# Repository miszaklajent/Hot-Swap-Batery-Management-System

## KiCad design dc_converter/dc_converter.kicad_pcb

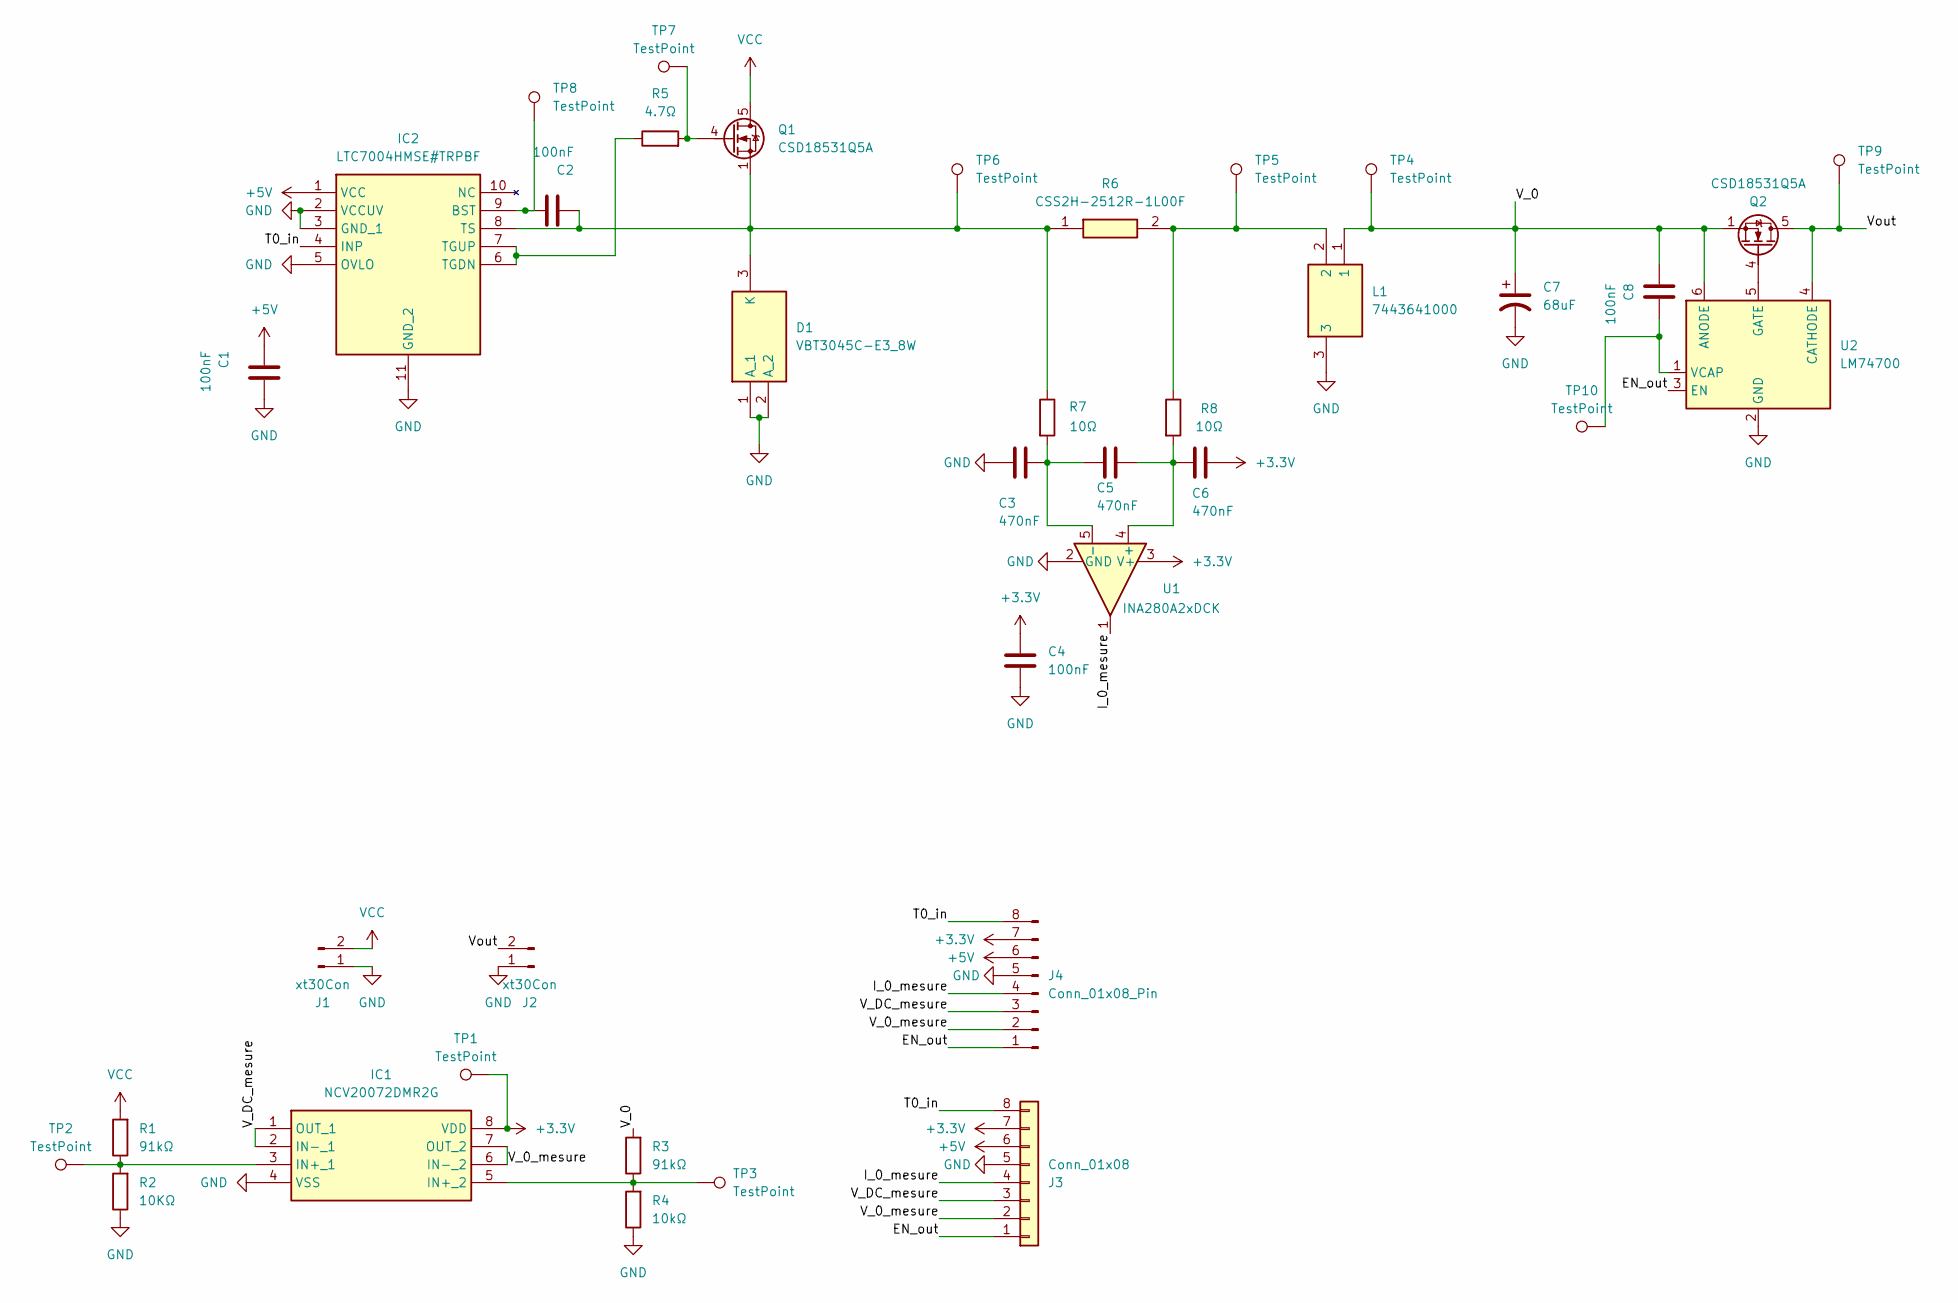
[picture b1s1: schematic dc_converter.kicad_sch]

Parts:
C1, C2, C4, C8: 100nF; C_0402_1005Metric
C3, C5, C6: 470nF; C_0402_1005Metric
C7: 68uF; CAPAE830X1050N
D1: VBT3045C-E3_8W; TO-263AB_1; Mouser Part Number 625-VBT3045C-E3/8W
IC1: NCV20072DMR2G; SOP65P490X110-8N; Mouser Part Number 863-NCV20072DMR2G
IC2: LTC7004HMSE#TRPBF; SOP50P490X110-11N; Mouser Part Number 584-7004HMSETRPBF
J1, J2: xt30Con; AMASS_XT30U-M_1x02_P5.0mm_Vertical
J3: Conn_01x08; JST_GH_SM08B-GHS-TB_1x08-1MP_P1.25mm_Horizontal
J4: Conn_01x08_Pin; PinHeader_1x08_P2.54mm_Vertical
L1: 7443641000; WE-HCF_SMD_HIGH-CURRENT_INDUCTOR; Mouser Part Number 710-7443641000
Q1, Q2: CSD18531Q5A; TDSON-8-1
R1, R3: 91kΩ; R_0402_1005Metric
R2: 10KΩ; R_0402_1005Metric
R4: 10kΩ; R_0402_1005Metric
R5: 4.7Ω; R_1206_3216Metric_Pad1.30x1.75mm_HandSolder
R6: CSS2H-2512R-1L00F; RESC6430X87N; Mouser Part Number 652-CSS2H2512R1L00F
R7, R8: 10Ω; R_0402_1005Metric
TP1, TP2, TP3, TP4, TP5, TP6, TP7, TP8, TP9, TP10: TestPoint; TestPoint_Pad_D1.0mm
U1: INA280A2xDCK; SOT-353_SC-70-5
U2: LM74700; SOT-23-6

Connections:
+3.3V: C4.2, C6.2, IC1.8 (VDD), J3.7, J4.7, TP1.1 (1_1), U1.3 (V+)
+5V: C1.1, IC2.1 (VCC), J3.6, J4.6
/EN_out: J3.1, J4.1, U2.3 (EN)
/I_0_mesure: J3.4, J4.4, U1.1
/T0_in: IC2.4 (INP), J3.8, J4.8
/V_0: C7.1, C8.1, L1.1, Q2.1 (S), Q2.2 (S), Q2.3 (S), R3.2, TP4.1 (1_1), U2.6 (ANODE)
/V_0_mesure: IC1.6 (IN-_2), IC1.7 (OUT_2), J3.2, J4.2
/V_DC_mesure: IC1.1 (OUT_1), IC1.2 (IN-_1), J3.3, J4.3
/Vout: J2.2, Q2.5 (D), TP9.1 (1_1), U2.4 (CATHODE); also elsewhere on the board
GND: C1.2, C3.1, C4.1, C7.2, D1.1 (A_1), D1.2 (A_2), IC1.4 (VSS), IC2.2 (VCCUV), IC2.3 (GND_1), IC2.5 (OVLO), IC2.11 (GND_2), J1.1, J2.1, J3.5, J4.5, L1.3, R2.1, R4.1, U1.2 (GND), U2.2 (GND); also elsewhere on the board
unnamed: C2.1, D1.3 (K), IC2.8 (TS), Q1.1 (S), Q1.2 (S), Q1.3 (S), R6.1, R7.1, TP6.1 (1_1)
unnamed: IC1.3 (IN+_1), R1.1, R2.2, TP2.1 (1_1)
unnamed: IC1.5 (IN+_2), R3.1, R4.2, TP3.1 (1_1)
unnamed: C2.2, IC2.9 (BST), TP8.1 (1_1)
unnamed: IC2.6 (TGDN), IC2.7 (TGUP), R5.1
unnamed: L1.2, R6.2, R8.1, TP5.1 (1_1)
unnamed: Q1.4 (G), R5.2, TP7.1 (1_1)
unnamed: Q2.4 (G), U2.5 (GATE)
unnamed: C5.2, C6.1, R8.2, U1.4 (+)
unnamed: C3.2, C5.1, R7.2, U1.5 (-)
unnamed: C8.2, TP10.1 (1_1), U2.1 (VCAP)
VCC: J1.2, Q1.5 (D), R1.2; also elsewhere on the board

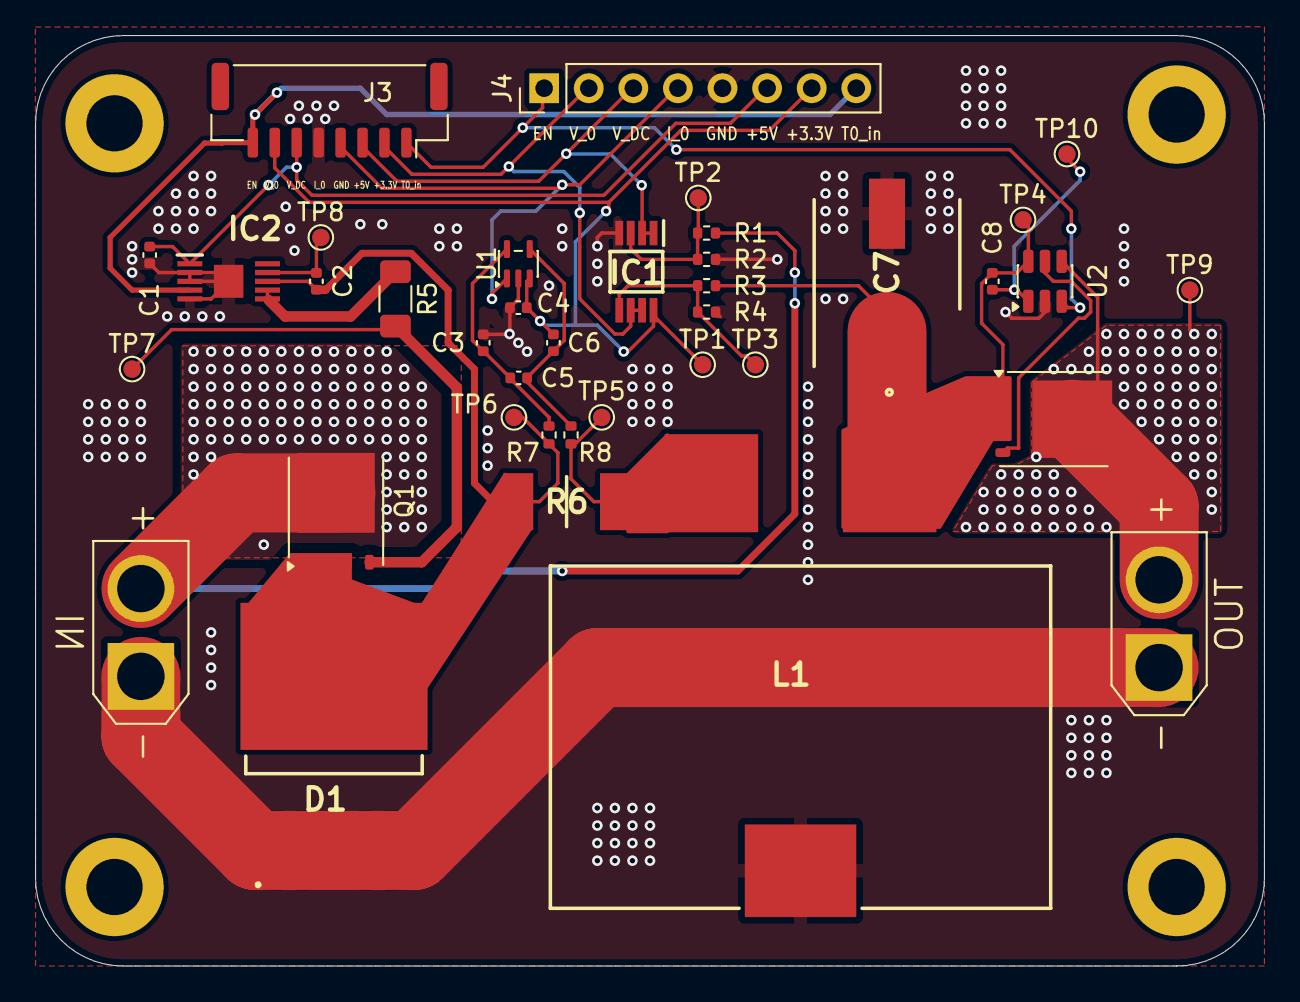
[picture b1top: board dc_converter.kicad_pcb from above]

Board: 2 copper layers, 70.0 x 53.0 mm, 38 parts (0 on the bottom side), 22 nets.

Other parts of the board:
IN: xt30Con; AMASS_XT30U-M_1x02_P5.0mm_Vertical
OUT: xt30Con; AMASS_XT30U-M_1x02_P5.0mm_Vertical

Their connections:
/Vout: OUT.2; also elsewhere on the board
GND: IN.1, OUT.1; also elsewhere on the board
VCC: IN.2; also elsewhere on the board
